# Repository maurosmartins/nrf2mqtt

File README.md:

# nrf2mqtt
IOT outdoor solar lamp with python bridge between Nordic NRF24L01+ and MQTT

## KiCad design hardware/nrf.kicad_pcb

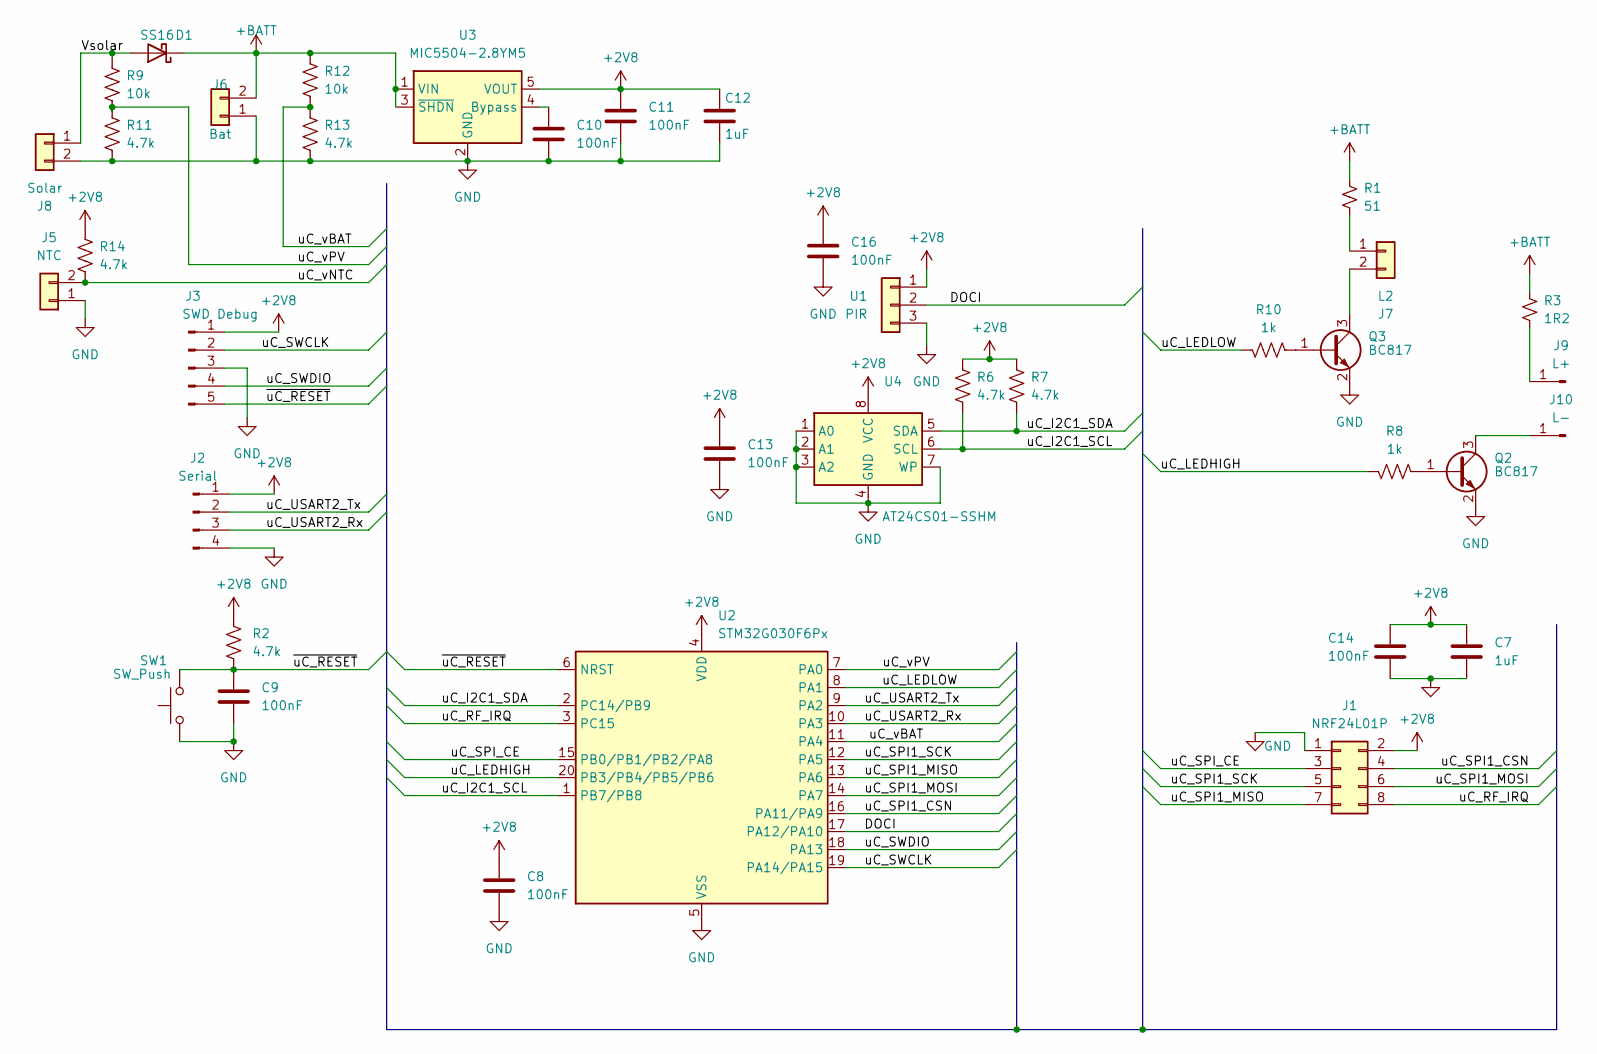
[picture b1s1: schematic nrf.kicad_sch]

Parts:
C7: 1uF; C_0603_1608Metric; LCSC#1 C106205
C8, C9, C10, C13, C16: 100nF; C_0603_1608Metric
C11: 100nF; C_0603_1608Metric; LCSC#1 C1525
C12: 1uF; C_0603_1608Metric; LCSC#1 C15525
C14: 100nF; C_0603_1608Metric; LCSC#1 C1524
D1: SS16; D_SMA
J1: NRF24L01P; PinHeader_2x04_P2.54mm_Vertical
J2: Serial; PinHeader_1x04_P2.54mm_Vertical
J3: SWD Debug; PinHeader_1x05_P2.54mm_Vertical; LCSC#1 C2935945
J5: NTC; JST_PH_S2B-PH-K_1x02_P2.00mm_Horizontal
J6: Bat; JST_XH_S2B-XH-A-1_1x02_P2.50mm_Horizontal
J7: L2; JST_PH_S2B-PH-K_1x02_P2.00mm_Horizontal
J8: Solar; JST_PH_S2B-PH-K_1x02_P2.00mm_Horizontal
J9: L+; PinHeader_1x01_P2.54mm_Vertical
J10: L-; PinHeader_1x01_P2.54mm_Vertical
Q2, Q3: BC817; SOT-23
R1: 51; R_1206_3216Metric
R2, R6, R7, R11, R13, R14: 4.7k; R_0603_1608Metric; LCSC#1 C2906869
R3: 1R2; R_1210_3225Metric
R8, R10: 1k; R_0603_1608Metric; LCSC#1 C226166
R9, R12: 10k; R_0603_1608Metric; LCSC#1 C2906869
SW1: SW_Push; SW_SPST_Omron_B3FS-101xP
U1: PIR; YS332
U2: STM32G030F6Px; TSSOP-20_4.4x6.5mm_P0.65mm; LCSC#1 C529330
U3: MIC5504-2.8YM5; SOT-23-5; LCSC#1 C88419
U4: AT24CS01-SSHM; SOIC-8_3.9x4.9mm_P1.27mm

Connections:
+2V8: C7.1, C8.1, C11.1, C12.1, C13.1, C14.1, C16.1, J1.2, J2.1, J3.1, R2.1, R6.1, R7.1, R14.1, U1.1, U2.4 (VDD), U3.5 (VOUT), U4.8 (VCC)
+BATT: D1.1 (K), J6.2, R1.2, R3.2, R12.1, U3.1 (VIN), U3.3 (~SHDN)
/DOCI: U1.2, U2.17 (PA12/PA10)
/Vsolar: D1.2 (A), J8.1, R9.1
/uC_I2C1_SCL: R6.2, U2.1 (PB7/PB8), U4.6 (SCL)
/uC_I2C1_SDA: R7.2, U2.2 (PC14/PB9), U4.5 (SDA)
/uC_LEDHIGH: R8.2, U2.20 (PB3/PB4/PB5/PB6)
/uC_LEDLOW: R10.2, U2.8 (PA1)
/uC_RF_IRQ: J1.8, U2.3 (PC15)
/uC_SPI1_CSN: J1.4, U2.16 (PA11/PA9)
/uC_SPI1_MISO: J1.7, U2.13 (PA6)
/uC_SPI1_MOSI: J1.6, U2.14 (PA7)
/uC_SPI1_SCK: J1.5, U2.12 (PA5)
/uC_SPI_CE: J1.3, U2.15 (PB0/PB1/PB2/PA8)
/uC_SWCLK: J3.2, U2.19 (PA14/PA15)
/uC_SWDIO: J3.4, U2.18 (PA13)
/uC_USART2_Rx: J2.3, U2.10 (PA3)
/uC_USART2_Tx: J2.2, U2.9 (PA2)
/uC_vBAT: R12.2, R13.1, U2.11 (PA4)
/uC_vNTC: J5.2, R14.2
/uC_vPV: R9.2, R11.1, U2.7 (PA0)
/~uC_RESET: C9.1, J3.5, R2.2, SW1.2, U2.6 (NRST)
GND: C7.2, C8.2, C9.2, C10.2, C11.2, C12.2, C13.2, C14.2, C16.2, J1.1, J2.4, J3.3, J5.1, J6.1, J8.2, Q2.2 (E), Q3.2 (E), R11.2, R13.2, SW1.1, U1.3, U2.5 (VSS), U3.2 (GND), U4.1 (A0), U4.2 (A1), U4.3 (A2), U4.4 (GND), U4.7 (WP)
unnamed: J7.1, R1.1
unnamed: J7.2, Q3.3 (C)
unnamed: J9.1, R3.1
unnamed: J10.1, Q2.3 (C)
unnamed: Q2.1 (B), R8.1
unnamed: Q3.1 (B), R10.1
unnamed: C10.1, U3.4 (Bypass)

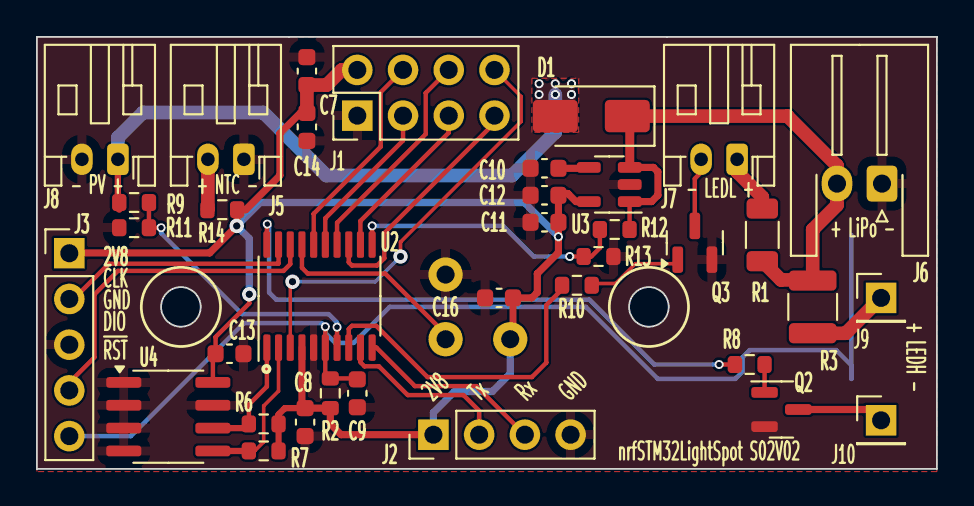
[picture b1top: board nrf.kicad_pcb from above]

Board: 2 copper layers, 50.0 x 24.0 mm, 38 parts (1 on the bottom side), 30 nets.

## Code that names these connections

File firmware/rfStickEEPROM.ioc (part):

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Mcu.Name=STM32G030F6Px
Mcu.Package=TSSOP20
Mcu.UserName=STM32G030F6Px
PA0.Mode=IN0
PA0.Signal=ADC1_IN0
PA1.Signal=GPIO_Input
PA11\ [PA9].GPIOParameters=GPIO_Label
PA11\ [PA9].GPIO_Label=NRF_CE
PA11\ [PA9].Signal=GPIO_Output
PA12\ [PA10].Signal=S_TIM1_ETR
PA13.Mode=Serial_Wire
PA13.Signal=SYS_SWDIO
PA14-BOOT0.Mode=Serial_Wire
PA14-BOOT0.Signal=SYS_SWCLK
PA14-BOOT0__PA15.StandardMode=true
PA2.Mode=Asynchronous
PA2.Signal=USART2_TX
PA3.Mode=Asynchronous
PA3.Signal=USART2_RX
PA4.GPIOParameters=GPIO_Label
PA4.GPIO_Label=NRF_IRQ
PA4.Signal=GPXTI4
PA5.Mode=Full_Duplex_Master
PA5.Signal=SPI1_SCK
PA6.Mode=Full_Duplex_Master
PA6.Signal=SPI1_MISO
PA7.Mode=Full_Duplex_Master
PA7.Signal=SPI1_MOSI
PB0.GPIOParameters=GPIO_Label
PB0.GPIO_Label=SPI1_CSN
PB0.Signal=GPIO_Output
PB0__PB1__PB2__PA8.StandardMode=true
PB3.GPIOParameters=GPIO_Label
PB3.GPIO_Label=OneWire
PB3.Signal=GPIO_Input
PB3__PB4__PB5__PB6.StandardMode=true
PB7__PB8.StandardMode=true
PB8.Mode=I2C
PB8.Signal=I2C1_SCL
PB9.Mode=I2C
PB9.Signal=I2C1_SDA
PC14-OSC32_IN\ (PC14)__PB9.StandardMode=true
PC15-OSC32_OUT\ (PC15).GPIOParameters=GPIO_Label
PC15-OSC32_OUT\ (PC15).GPIO_Label=MPU_INT
PC15-OSC32_OUT\ (PC15).Signal=GPXTI15
RCC.HSE_VALUE=8000000
RCC.SYSCLKFreq_VALUE=32000000
RCC.SYSCLKSource=RCC_SYSCLKSOURCE_PLLCLK
board=custom

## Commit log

2026-05-03 NRF24L01p PCB information added
    PCB information added
2026-05-03 STM32G030 firmware added
    STM32G030 firmware added
2026-05-03 added schematic print
